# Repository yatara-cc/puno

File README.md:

# Yatara Puno

A modular system for reusable, adjustable hand-wired keyboards.

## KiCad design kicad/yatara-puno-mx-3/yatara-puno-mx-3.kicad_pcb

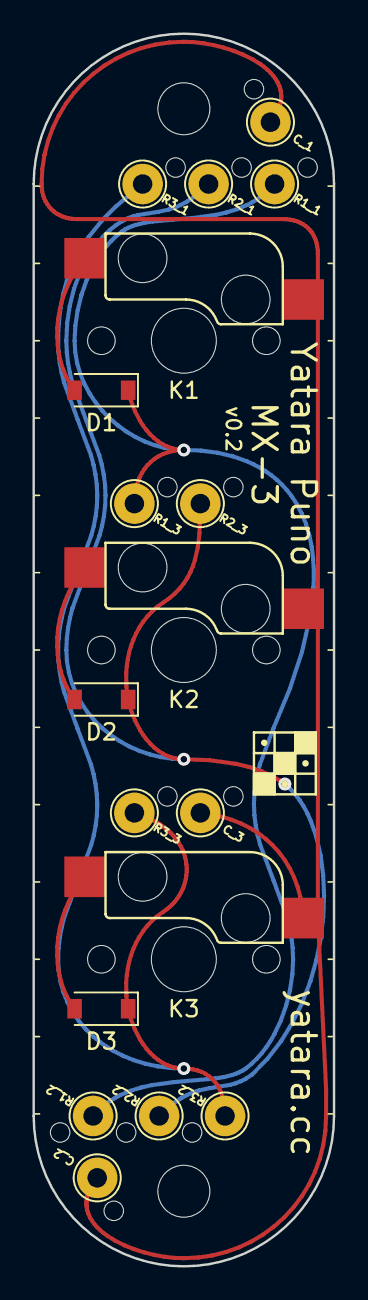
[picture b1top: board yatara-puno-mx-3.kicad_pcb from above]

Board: 2 copper layers, 18.5 x 75.9 mm, 18 parts (0 on the bottom side), 7 nets.

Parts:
C_1, C_2, C_3: TestPoint; TestPoint_THTPad_D2.5mm_Drill1.2mm
D1, D2, D3: D; D_SOD-123
K1, K2, K3: KEYSW; Kailh_PCB_Socket_1511_MX
R1_1, R1_2, R1_3, R2_1, R2_2, R2_3, R3_1, R3_2, R3_3: TestPoint; TestPoint_THTPad_D2.5mm_Drill1.2mm

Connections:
unnamed: C_1.1, C_2.1, C_3.1, K1.1, K2.1, K3.1
unnamed: D1.1, R1_1.1, R1_2.1, R1_3.1
unnamed: D1.2, K1.2
unnamed: D2.1, R2_1.1, R2_2.1, R2_3.1
unnamed: D2.2, K2.2
unnamed: D3.1, R3_1.1, R3_2.1, R3_3.1
unnamed: D3.2, K3.2

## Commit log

2019-02-10 Initial commit. Adding Puno MX-5 v0.2.
2019-02-10 Add minimal README.
2019-02-10 Rename traces SVG.
2019-02-10 Add Puno MX-4 v0.2.
2019-02-10 Add Puno MX-3 v0.2.
2019-02-10 Add Gerber and drill files.
